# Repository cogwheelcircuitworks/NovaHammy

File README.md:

# NovaHammy
Break-out &amp; interface board for the Dorji DRA818 amateur radio transceiver modules !

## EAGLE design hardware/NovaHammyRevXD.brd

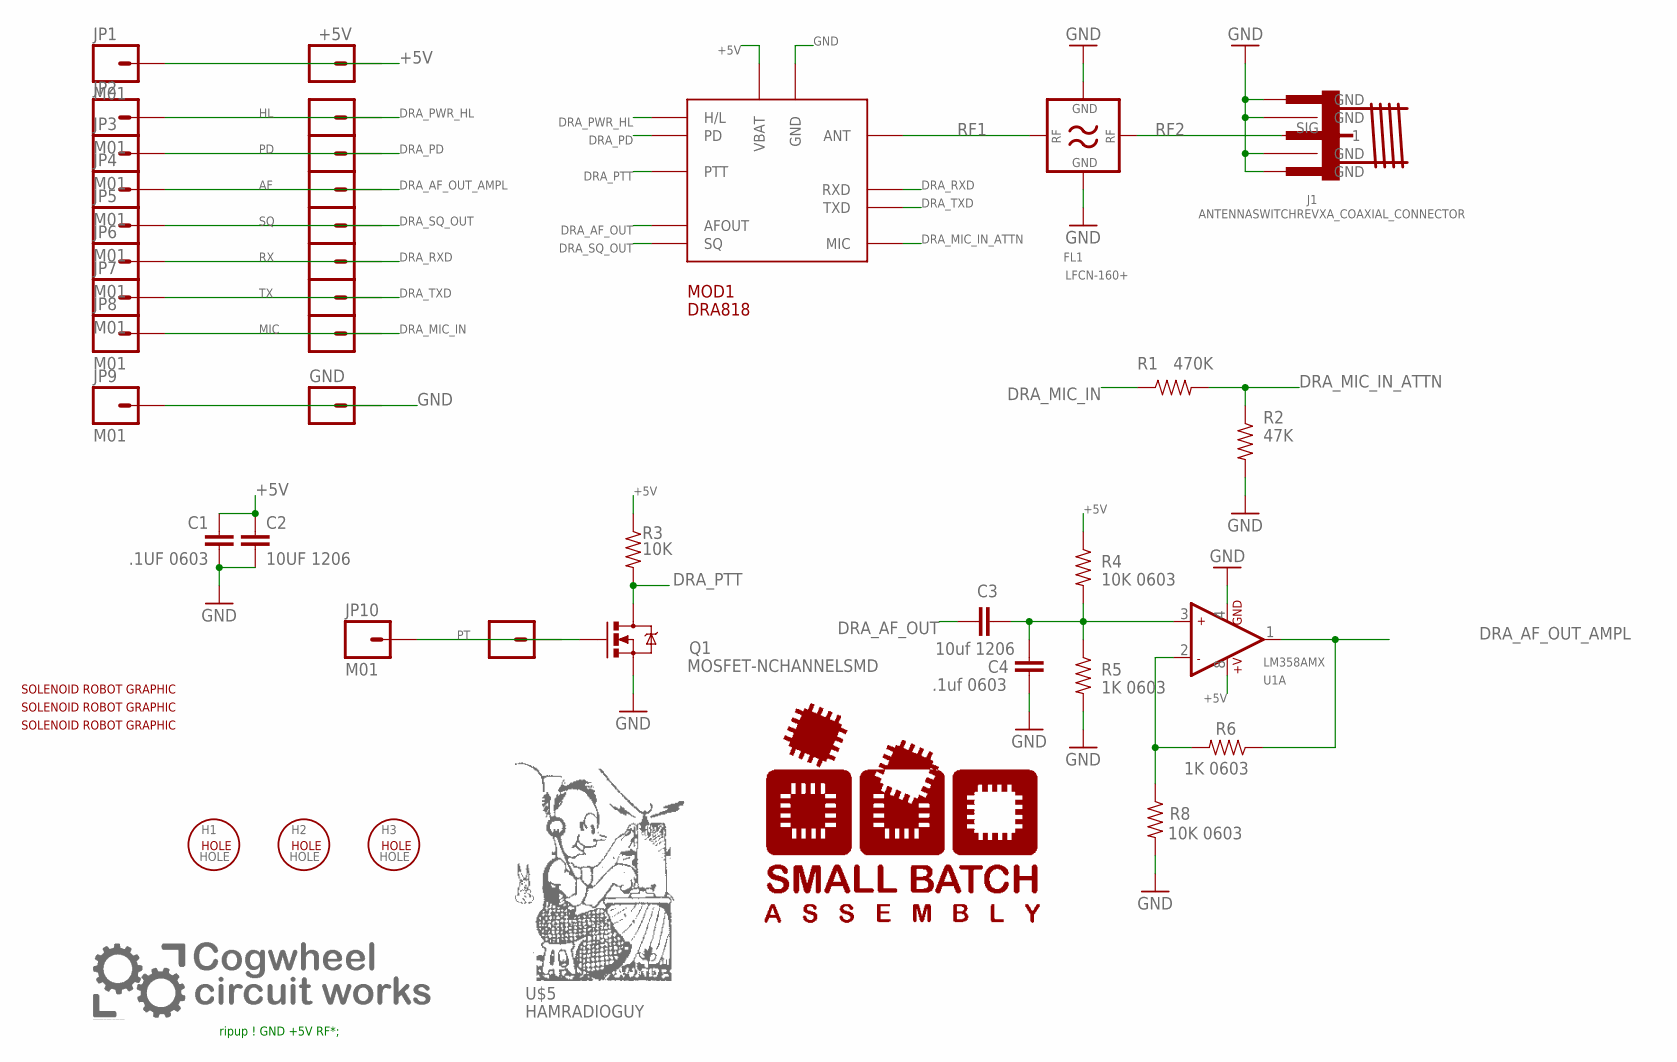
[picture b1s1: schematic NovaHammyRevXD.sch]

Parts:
5V: +5V; 1X01_NO_SILK
AF: M01PTH_NO_SILK_YES_STOP; 1X01_NO_SILK
C1: .1UF 0603; 0603
C2: 10UF 1206; 1206
C3: 10uf 1206; 1206
C4: .1uf 0603; 0603
FL1: LFCN-160+; FV1206
GND: M01PTH_NO_SILK_YES_STOP; 1X01_NO_SILK
H1, H2, H3: HOLE; HOLE_3.3MM_M3_HEX_BOLT
HL: M01PTH_NO_SILK_YES_STOP; 1X01_NO_SILK
J1: ANTENNASWITCHREVXA_COAXIAL_CONNECTOR; ANTENNASWITCHREVXA_SMA_JACK_EDGE_MOUNT
JP1, JP2, JP3, JP4, JP5, JP6, JP7, JP8, JP9, JP10: M01; 1X01_SMT_2MM
MIC: M01PTH_NO_SILK_YES_STOP; 1X01_NO_SILK
MOD1: DRA818
PD: M01PTH_NO_SILK_YES_STOP; 1X01_NO_SILK
PT: M01PTH_NO_SILK_YES_STOP; 1X01_NO_SILK
Q1: MOSFET-NCHANNELSMD; SOT23-3
R1: 470K; 0603
R2: 47K; 0603
R3: 10K; 0603
R4, R8: 10K 0603; 0603
R5, R6: 1K 0603; 0603
RX: M01PTH_NO_SILK_YES_STOP; 1X01_NO_SILK
SQ: M01PTH_NO_SILK_YES_STOP; 1X01_NO_SILK
TX: M01PTH_NO_SILK_YES_STOP; 1X01_NO_SILK
U1: LM358AMX; SOIC8
U$1, U$2, U$3: SOLENOID_ROBOTSML; SOLENOID_ROBOT
U$4: SMALLBATCH_LOGOA; SMALLBATCH_750W_V2
U$5: HAMRADIOGUY; HAMRADIO_3Q_INCH
U$6: CWILOGO; CWORKSLOGO_750MIL_WIDE_400DPI

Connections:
+5V: 5V.1, C1.2, C2.1, JP1.P$1, MOD1.P$8 (VBAT), R3.1, R4.1, U1.8 (+V)
DRA_AF_OUT: C3.1, MOD1.P$3 (AFOUT)
DRA_AF_OUT_AMPL: AF.1, JP4.P$1, R6.1, U1.1 (OUT1)
DRA_MIC_IN: JP8.P$1, MIC.1, R1.1
DRA_MIC_IN_ATTN: MOD1.P$18 (MIC), R1.2, R2.1
DRA_PD: JP3.P$1, MOD1.P$6 (PD), PD.1
DRA_PTT: MOD1.P$5 (PTT), Q1.3 (D), R3.2
DRA_PWR_HL: HL.1, JP2.P$1, MOD1.P$7 (H/L)
DRA_RXD: JP6.P$1, MOD1.P$16 (RXD), RX.1
DRA_SQ_OUT: JP5.P$1, MOD1.P$1 (SQ), SQ.1
DRA_TXD: JP7.P$1, MOD1.P$17 (TXD), TX.1
GND: C1.1, C2.2, C4.2, FL1.2 (GND2), FL1.4 (GND1), FL1.6 (GND1), FL1.7 (GND1), FL1.8 (GND1), FL1.9 (GND1), FL1.11 (GND2), FL1.12 (GND2), FL1.13 (GND2), FL1.14 (GND2), GND.1, J1.G (GND), J1.G2 (GND), J1.G3 (GND), J1.G4 (GND), JP9.P$1, MOD1.P$9 (GND), MOD1.P$10 (GND), Q1.2 (S), R2.2, R5.2, R8.2, U1.4 (GND)
unnamed: C3.2, C4.1, R4.2, R5.1, U1.3 (+IN1)
unnamed: R6.2, R8.1, U1.2 (-IN1)
unnamed: JP10.P$1, PT.1, Q1.1 (G)
RF1: FL1.1 (IO1), MOD1.P$12 (ANT)
RF2: FL1.3 (IO2), J1.SIG (1)

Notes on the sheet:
ripup ! GND +5V RF*;

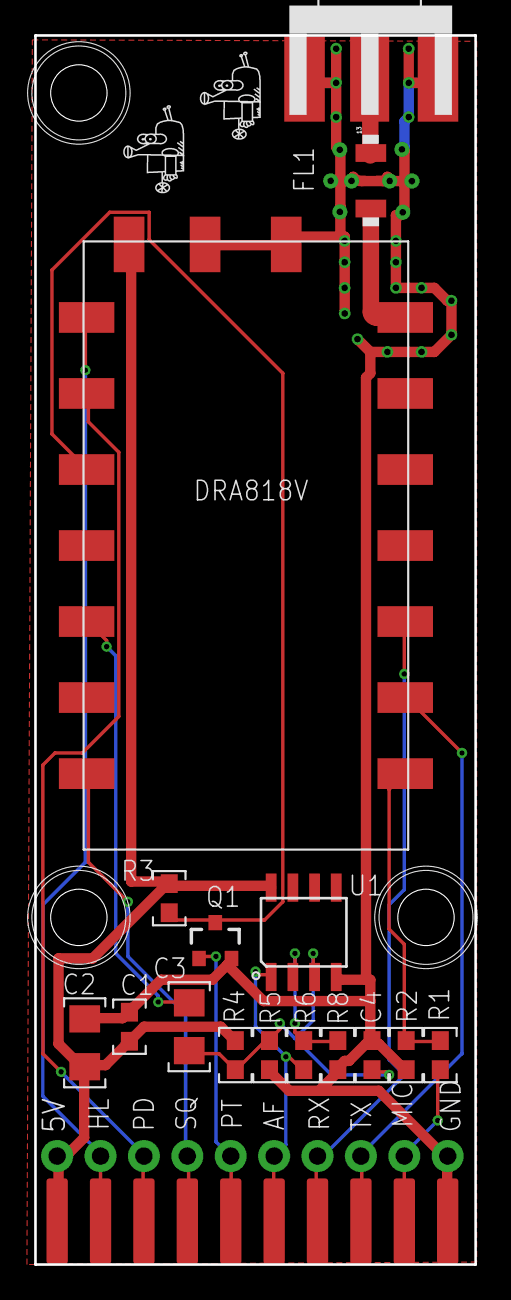
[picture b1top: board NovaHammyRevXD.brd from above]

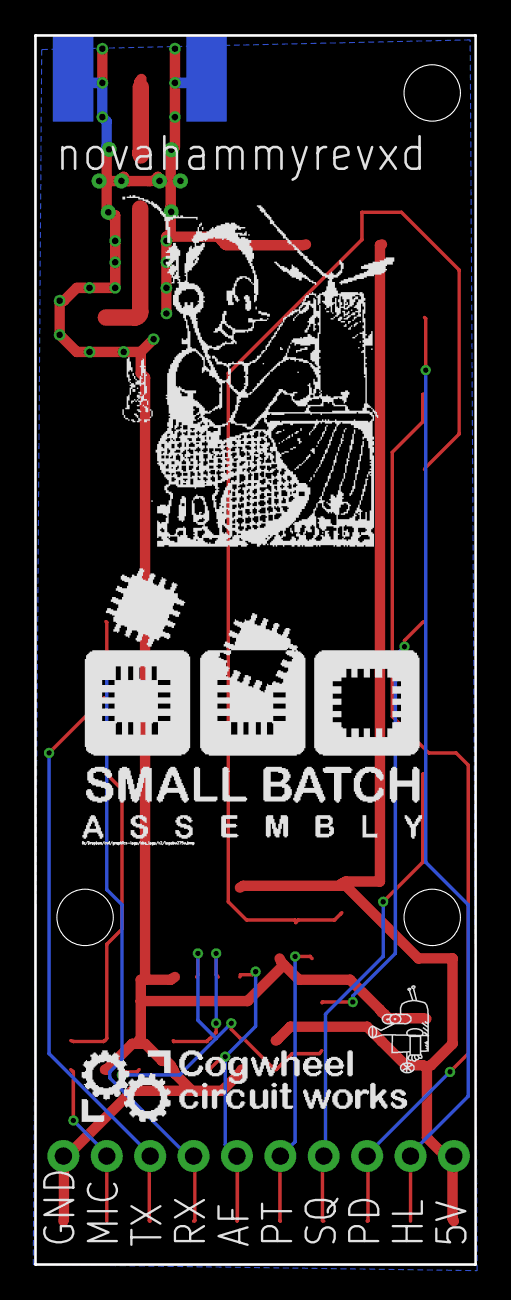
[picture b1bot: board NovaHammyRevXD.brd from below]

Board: 2 copper layers, 25.8 x 71.9 mm, 45 parts (4 on the bottom side), 17 nets.

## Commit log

2016-09-11 new file: hardware/NovaHammyRevXD.brd new file: hardware/NovaHammyRevXD.sch new file: hardware/NovaHammyRevXDsch.pdf new file: software/.vimrc new file: software/AudioIO.cpp new file: software/AudioI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
2017-09-28 -Break-out &amp; interface board for the Dorji DRA818 amateur radio transceiver modules +Break-out &amp; interface board for the Dorji DRA818 amateur radio transceiver modules !
